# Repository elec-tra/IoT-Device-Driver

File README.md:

# IoT-Device-Driver

This is an IoT Device contoller Schematic and PCB based on ESP8266

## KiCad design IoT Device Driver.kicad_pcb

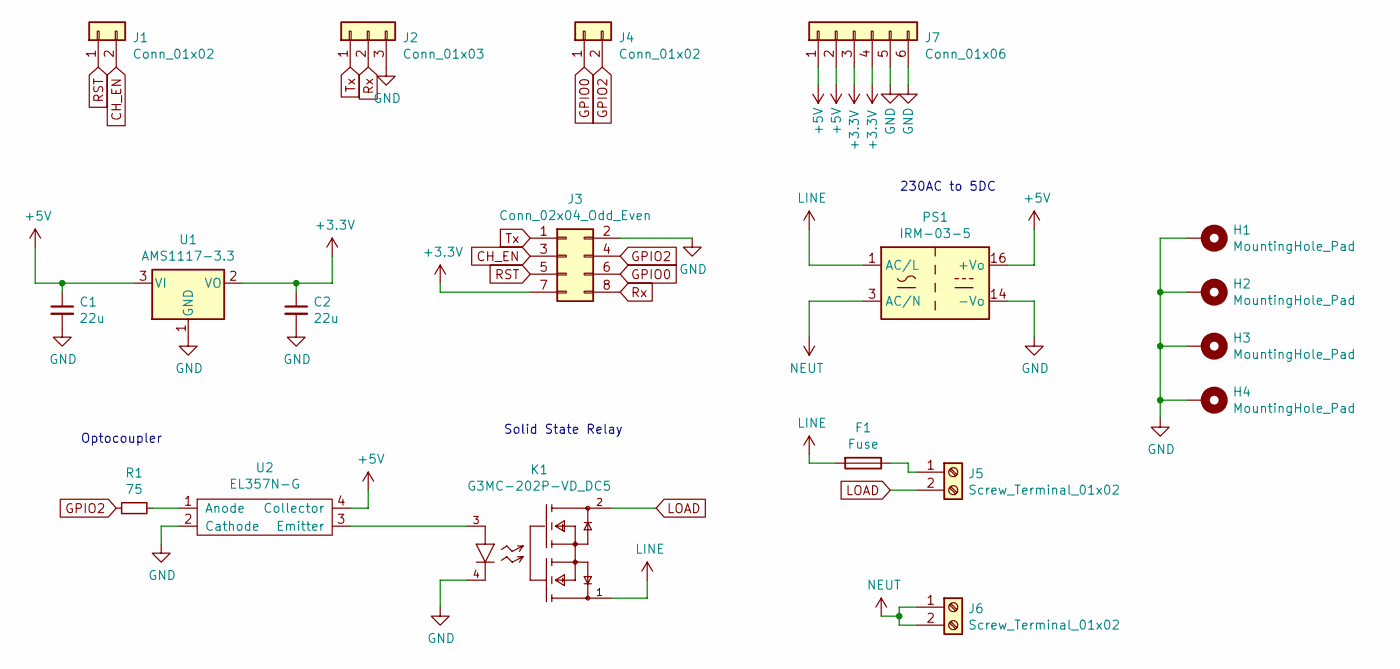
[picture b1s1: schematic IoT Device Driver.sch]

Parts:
C1, C2: 22u; C_0603_1608Metric
F1: Fuse; Fuseholder_Cylinder-5x20mm_Schurter_0031_8201_Horizontal_Op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
H1, H2, H3, H4: MountingHole_Pad; MountingHole_4.3mm_M4_Pad_Via
J1, J4: Conn_01x02; PinSocket_1x02_P2.54mm_Vertical
J2: Conn_01x03; PinSocket_1x03_P2.54mm_Vertical
J3: Conn_02x04_Odd_Even; PinHeader_2x04_P2.54mm_Vertical
J5, J6: Screw_Terminal_01x02; TerminalBlock_Phoenix_PT-1,5-2-5.0-H_1x02_P5.00mm_Horizontal
J7: Conn_01x06; PinSocket_1x06_P2.54mm_Vertical
K1: G3MC-202P-VD_DC5; Omron-G3MC-202P-VD_DC12-MFG; output voltage 264V; mouser part number 653-G3MC202P-VDDC12; digikey description RELAY SSR SPST-NO SIP 12VDC
PS1: IRM-03-5; Converter_ACDC_MeanWell_IRM-03-xx_SMD
R1: 75; R_1206_3216Metric
U1: AMS1117-3.3; SOT-223-3_TabPin2
U2: EL357N-G; EL357N_G-2.54SOP4P

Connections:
+3V3: C2.1, J3.7, J7.3, J7.4, U1.2 (VO)
+5V: C1.1, J7.1, J7.2, PS1.16 (+Vo), U1.3 (VI), U2.4 (Collector)
CH_EN: J1.2, J3.3
GND: C1.2, C2.2, H1.1, H2.1, H3.1, H4.1, J2.3, J3.2, J7.5, J7.6, K1.4 (-), PS1.14 (-Vo), U1.1 (GND), U2.2 (Cathode)
GPIO0: J3.6, J4.1
GPIO2: J3.4, J4.2, R1.2
LINE: F1.2, K1.1 (1_LOAD), PS1.1 (AC/L)
LOAD: J5.2, K1.2 (2_LOAD)
NEUT: J6.1, J6.2, PS1.3 (AC/N)
unnamed: F1.1, J5.1
unnamed: K1.3 (+), U2.3 (Emitter)
unnamed: R1.1, U2.1 (Anode)
RST: J1.1, J3.5
Rx: J2.2, J3.8
Tx: J2.1, J3.1

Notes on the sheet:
Optocoupler
Solid State Relay
230AC to 5DC

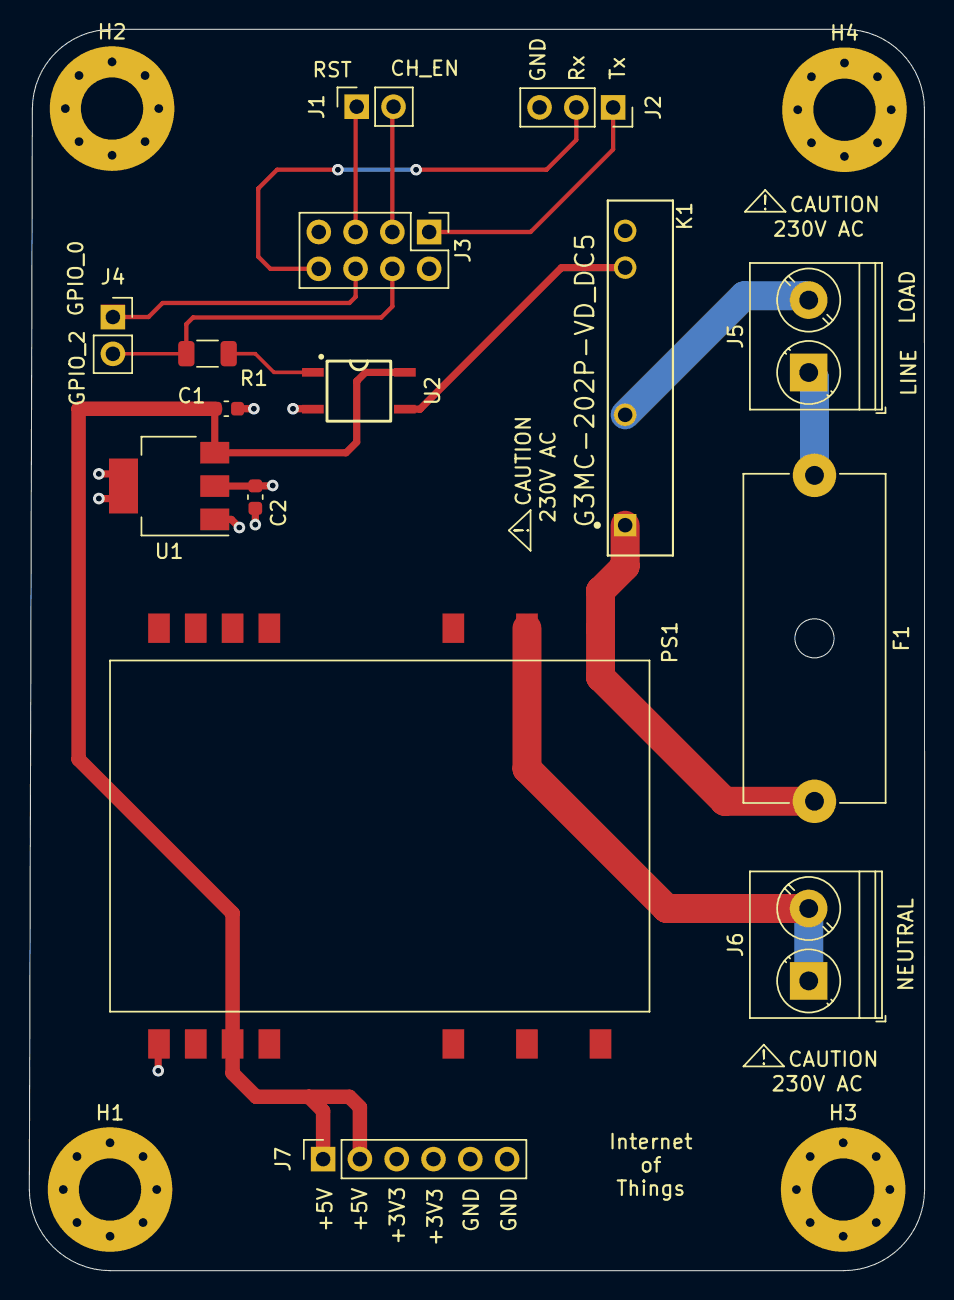
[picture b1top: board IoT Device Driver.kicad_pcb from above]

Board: 4 copper layers, 61.8 x 85.7 mm, 19 parts (0 on the bottom side), 15 nets.

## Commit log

2021-09-17 Power circuitry over
2021-09-20 assignment of footprint over except optocoupler
2021-09-21 Components alignment in PCB
2021-09-21 gitignore added
2021-09-21 removing unnecessary files
2021-09-21 committed only necessary files
2021-09-22 Routing
    Routing for low power components over. Things to do: 1)Edit copper fill area, 2(Calculate track width for 3A, 3)Lay track for high power components on bottom layer only
2021-09-23 PCB Version 1.0 over
2021-09-23 pcb image added
2021-09-23 image modified
